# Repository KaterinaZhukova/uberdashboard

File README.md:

echo "# uberdashboard" >> README.md
git init
git add README.md
git commit -m "first commit"
git remote add origin https://github.com/KaterinaZhukova/uberdashboard.git
git push -u origin master# uberdashboard

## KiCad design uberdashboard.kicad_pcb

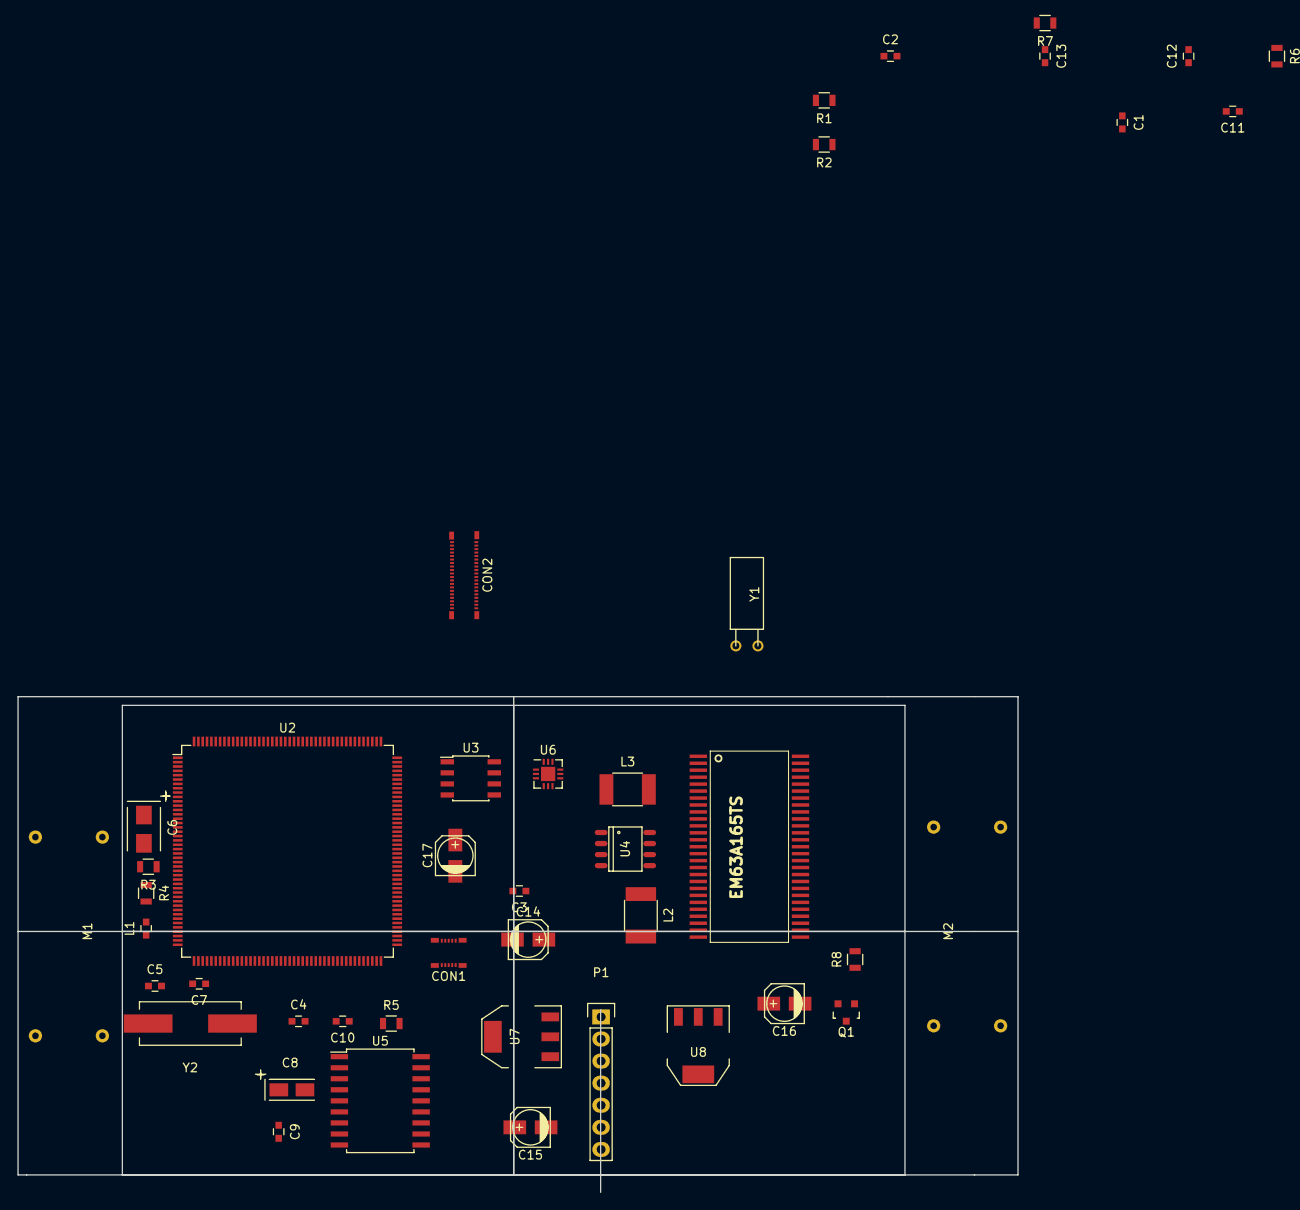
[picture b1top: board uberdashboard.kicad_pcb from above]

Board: 2 copper layers, 115.0 x 57.0 mm, 44 parts (0 on the bottom side), 108 nets, no tracks yet.

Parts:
C1, C10: 2.2uF; C_0603
C2, C3: 6.8pF; C_0603
C4, C5: 20pF; C_0603
C6: 1uF; TantalC_SizeB_EIA-3528_Wave
C7, C9: 100nF; C_0603
C8: 1uF; TantalC_SizeA_EIA-3216_Wave
C11: 10uF; C_0603
C12: 2x10uF; C_0603
C13: 1uF; C_0603
C14, C15, C16, C17: 10uF; c_elec_4x5.3
CON1: TOUCH-BM10NB(0.8)-10DS-0.4V(51); BM10NB(0.8)-10DS-0.4V(51)
CON2: AMOLED-BM10NB(0.8)-40DS-0.4V(51); BM10NB(0.8)-40DS-0.4V(51)
L1: INDUCTOR; C_0603
L2, L3: 4.7uH; R_1812
M1, M2: VID23-03; VID23
P1: CONN_ROUNDX07; Pin_Header_Straight_1x07
Q1: BC817-40; SOT-23
R1, R2, R3: 0; R_0805
R4: 220; R_0805
R5: R; R_0805
R6, R7: 10K; R_0805
R8: 1K; R_0805
U1: EM63A165TS; TSOP54
U2: STM32F429II; LQFP-176_24x24mm_Pitch0.5mm
U3: MX25L3206E; SOIC-8_3.9x4.9mm_Pitch1.27mm
U4: MCP2551-I/SN; SO-8
U5: MCP23008; SOIC-18_7.5x11.6mm_Pitch1.27mm
U6: STOD13AS; QFN-12-1EP_3x3mm_Pitch0.5mm
U7: LD1117S50TR; SOT-223
U8: LD1117S33TR; SOT-223
Y1: 32.768; Crystal_Watch
Y2: 8MHz; Crystal_HC49-SD_SMD

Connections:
+5V: C15.1, CON1.3, CON1.5, R5.2, U4.3, U5.18, U7.2
+12V: C14.1, C16.1, P1.1, U7.3, U8.3
/A0: U1.23, U2.16
/A1: U1.24, U2.17
/A2: U1.25, U2.18
/A3: U1.26, U2.19
/A4: U1.29, U2.20
/A5: U1.30, U2.21
/A6: U1.31, U2.60
/A7: U1.32, U2.63
/A8: U1.33, U2.64
/A9: U1.34, U2.65
/A10: U1.22, U2.66
/A11: U1.35, U2.67
/A12: U1.36, U2.106
/B0: CON2.34, U2.150
/B1: CON2.33, U2.154
/B2: CON2.32, U2.155
/B3: CON2.31, U2.47
/B4: CON2.30, U2.167
/B5: CON2.29, U2.168
/BA0: U1.20, U2.108
/BA1: U1.21, U2.109
/CAS#: U1.17, U2.160
/CKE: U1.37, U2.163
/CLK: U1.38, U2.112
/CS#: U1.19, U2.164
/CSB: CON2.37, U2.55
/D0: U1.2, U2.104
/D1: U1.4, U2.105
/D2: U1.5, U2.142
/D3: U1.7, U2.143
/D4: U1.8, U2.68
/D5: U1.10, U2.69
/D6: U1.11, U2.70
/D7: U1.13, U2.73
/D8: U1.42, U2.74
/D9: U1.44, U2.75
/D10: U1.45, U2.76
/D11: U1.47, U2.77
/D12: U1.48, U2.78
/D13: U1.50, U2.96
/D14: U1.51, U2.97
/D15: U1.53, U2.98
/EN: CON2.12, U2.28
/G0: CON2.28, U2.52
/G1: CON2.27, U2.153
/G2: CON2.26, U2.79
/G3: CON2.25, U2.80
/G4: CON2.24, U2.116
/G5: CON2.23, U2.145
/HSYNC: CON2.9, U2.115
/IRQ: CON1.9, U2.83
/MISO: U2.133, U3.2
/NBL0: U1.15, U2.169
/NBL1: U1.39, U2.170
/NSS: U2.131, U3.1
/PCLK: CON2.8, U2.111
/R0: CON2.22, U2.139
/R1: CON2.21, U2.56
/R2: CON2.20, U2.122
/R3: CON2.19, U2.123
/R4: CON2.18, U2.57
/R5: CON2.17, U2.110
/RAS#: U1.18, U2.59
/RESETB: CON2.15, U2.58
/SCK: U2.132, U3.6
/SCL: CON1.7, CON2.40, U2.25, U2.45, U2.84, U5.1
/SDA: CON1.8, U2.46, U2.85, U5.2
/SDI: CON2.35, U2.27
/VSYNC: CON2.11, U2.50
/WE#: U1.16, U2.32
GND: C1.1, C2.2, C3.2, C4.2, C5.2, C6.1, C7.1, C8.2, C9.2, C10.2, C11.2, C12.2, C13.2, C14.2, C15.2, C16.2, C17.2, CON1.1, CON1.6, CON1.10, CON2.6, CON2.10, CON2.14, CON2.38, CON2.39, L3.2, P1.6, Q1.2, R6.2, U1.6, U1.12, U1.28, U1.41, U1.46, U1.52, U1.54, U2.14, U2.22, U2.37, U2.61, U2.71, U2.90, U2.102, U2.113, U2.126, U2.135, U2.148, U2.158, U3.4, U4.2, U4.8, U5.3, U5.4, U5.5, U5.9, U6.2, U6.5, U6.13, U7.1, U8.1
unnamed: C1.2, U2.125
unnamed: C2.1, R1.2, Y1.1
unnamed: C3.1, R2.2, Y1.2
unnamed: C4.1, R3.2, Y2.1
unnamed: C5.1, R4.2, Y2.2
unnamed: C6.2, C7.2, U2.38
unnamed: C8.1, C9.1, L1.1, U2.39
unnamed: C10.1, U2.81
unnamed: C11.1, CON2.1, CON2.3, U6.3
unnamed: C12.1, CON2.2, CON2.4, U6.9
unnamed: C13.1, U6.6
unnamed: CON2.13, R6.1
unnamed: CON2.36, R8.2
unnamed: L2.1, U6.1
unnamed: L3.1, U6.10
unnamed: M1.1, U5.14
unnamed: M1.2, U5.15
unnamed: M1.3, U5.16
unnamed: M1.4, U5.17
unnamed: M2.1, U5.10
unnamed: M2.2, U5.11
unnamed: M2.3, U5.12
unnamed: M2.4, U5.13
unnamed: P1.2, U4.7
unnamed: P1.7, U4.6
unnamed: Q1.1, R8.1
unnamed: Q1.3, R7.2, U6.8
unnamed: R1.1, U2.9
unnamed: R2.1, U2.10
unnamed: R3.1, U2.29
unnamed: R4.1, U2.30
unnamed: R5.1, U5.6
unnamed: U2.92, U4.4
unnamed: U2.93, U4.1
VDD: C17.1, CON2.5, CON2.7, CON2.16, L1.2, L2.2, R7.1, U1.1, U1.3, U1.9, U1.14, U1.27, U1.43, U1.49, U2.15, U2.23, U2.36, U2.49, U2.62, U2.72, U2.82, U2.91, U2.103, U2.114, U2.127, U2.136, U2.149, U2.159, U2.171, U2.172, U3.3, U3.7, U3.8, U6.11, U6.12, U8.2

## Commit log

2016-03-16 Added files via upload
